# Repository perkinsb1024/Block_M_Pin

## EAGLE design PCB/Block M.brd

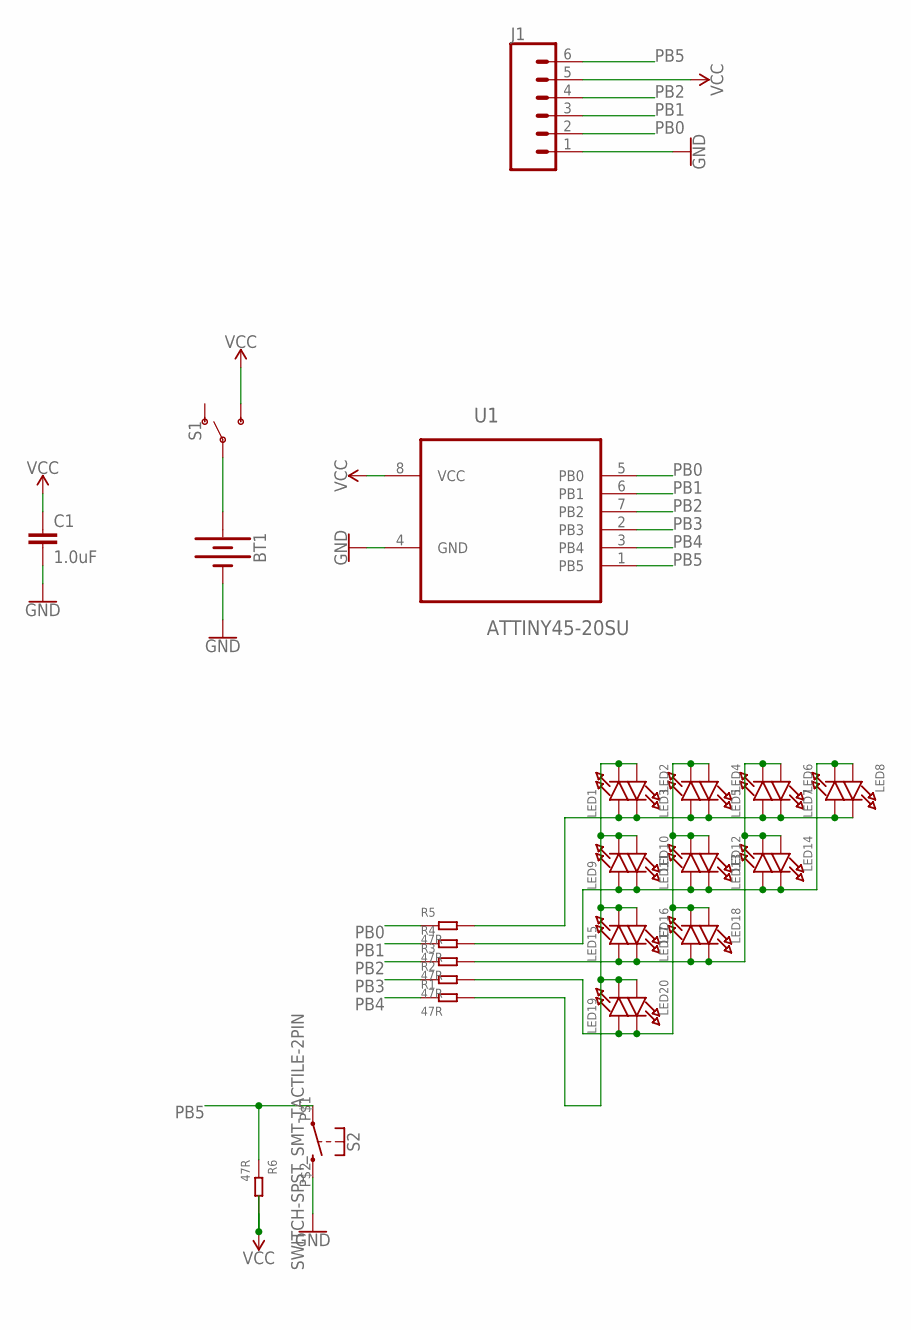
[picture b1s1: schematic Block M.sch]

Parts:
BT1: BATTERY-12MM_SMD_ALT; BATTCON_12MM_ALT
C1: 1.0uF; 0805
J1: CONN_06SMD-FEMALE-NO-SILK; 1X06-SMD-FEMALE_NO_SILK
LED1, LED2, LED3, LED4, LED5, LED6, LED7, LED8, LED9, LED10, LED11, LED12, LED13, LED14, LED15, LED16, LED17, LED18, LED19, LED20: LED0805_NOOUTLINE; CHIPLED_0805_NOOUTLINE
R1, R2, R3, R4, R5, R6: 47R; R0805
S1: SWITCH-SPDT-SMD-RIGHT-ANGLE; SWITCH_SPST_SMD_A
S2: SWITCH-SPST_SMT-TACTILE-2PIN; SMT_TACTILE_SWITCH_3X2MM
U1: ATTINY45-20SU; SOIC127P798X216-8N

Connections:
GND: BT1.GND (-), C1.2, J1.1, S2.P$2 (2), U1.4 (GND)
unnamed: LED1.A, LED2.C, LED3.A, LED4.C, LED5.A, LED6.C, LED7.A, LED8.C, R5.2
unnamed: BT1.PWR@2 (+), S1.2
unnamed: LED3.C, LED4.A, LED11.C, LED12.A, LED17.C, LED18.A, LED19.A, LED20.C, R2.2
unnamed: LED5.C, LED6.A, LED13.C, LED14.A, LED15.A, LED16.C, LED17.A, LED18.C, R3.2
unnamed: LED1.C, LED2.A, LED9.C, LED10.A, LED15.C, LED16.A, LED19.C, LED20.A, R1.2
unnamed: LED7.C, LED8.A, LED9.A, LED10.C, LED11.A, LED12.C, LED13.A, LED14.C, R4.2
PB0: J1.2, R5.1, U1.5 (PB0)
PB1: J1.3, R4.1, U1.6 (PB1)
PB2: J1.4, R3.1, U1.7 (PB2)
PB3: R2.1, U1.2 (PB3)
PB4: R1.1, U1.3 (PB4)
PB5: J1.6, R6.1, S2.P$1 (1), U1.1 (PB5)
VCC: C1.1, J1.5, R6.2, S1.3 (S), U1.8 (VCC)

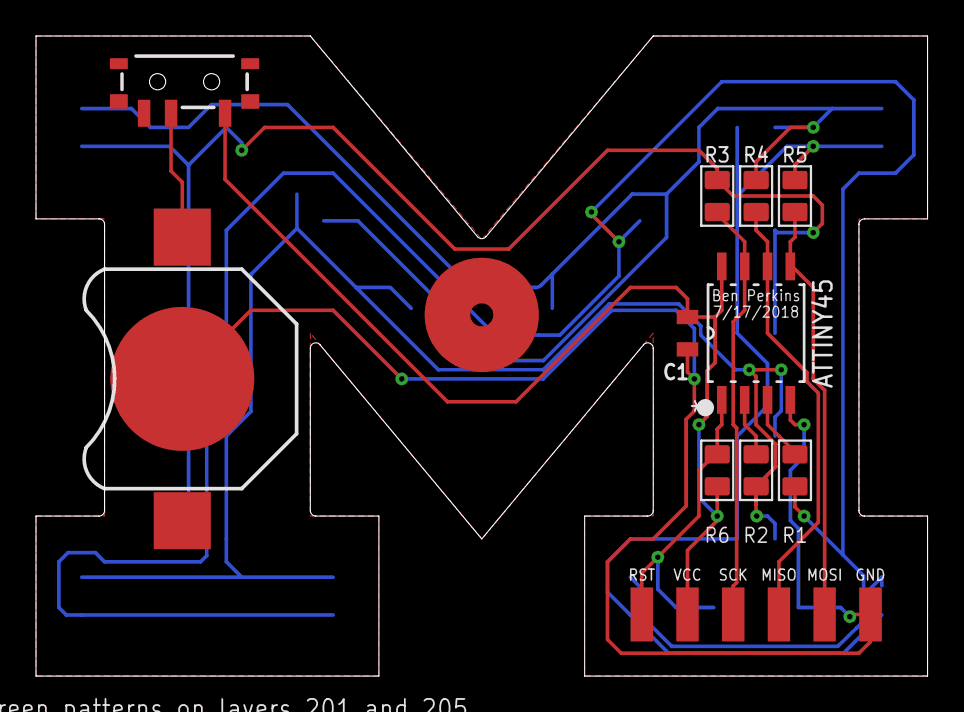
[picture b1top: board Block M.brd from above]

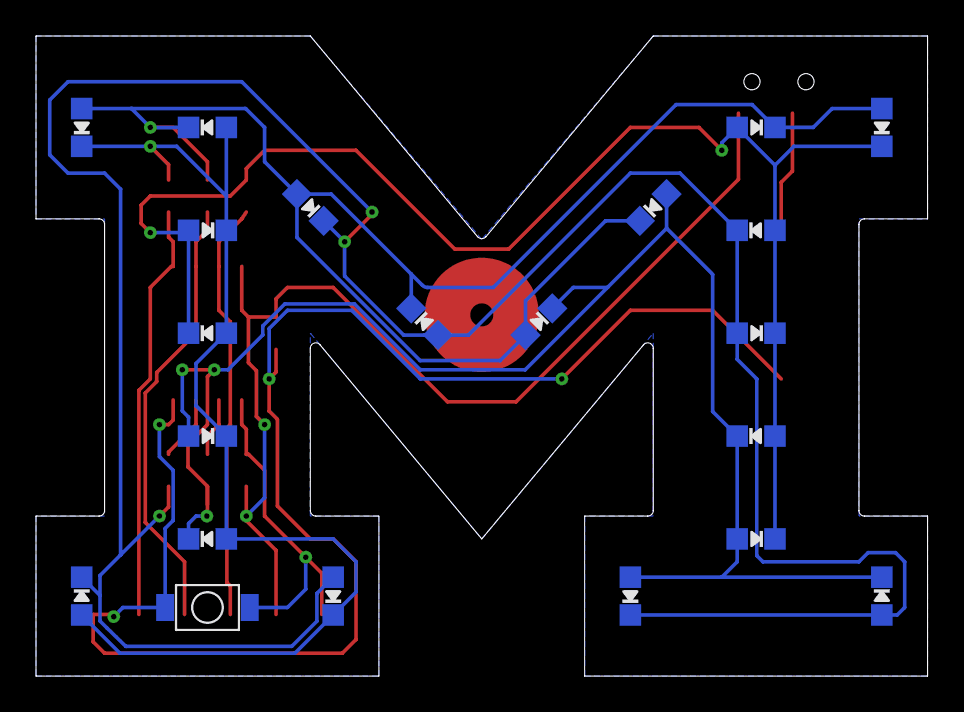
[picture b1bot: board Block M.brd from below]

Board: 2 copper layers, 49.5 x 35.6 mm, 32 parts (21 on the bottom side), 14 nets.

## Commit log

2018-07-28 Functional Charlie-Plexing. Could use some improvement
2018-07-28 Improved charlieplex logic. Reduced program size by 114 bytes (increased globals by 22 bytes). Improved speed and brightness
2018-07-30 Added more patterns and reduced MCU power consumption
2018-08-01 Added more patterns
2018-08-01 Improved 'boom' pattern
2018-08-01 Improved fade function
2018-08-01 Store seed for pRNG in EEPROM for more variability in 'randomness'
2018-08-05 Added function comments, cleaned code
2018-08-06 Added PCB files (Eagle and Gerber)
2018-08-06 Move Arduino Sketch into folder with the same name

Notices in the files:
parts and their libraries:
SparkFun-Switches: Licensing: Creative Commons ShareAlike 4.0 International - https://creativecommons.org/licenses/by-sa/4.0
microbuilder: This work is placed in the public domain, and may be freely used for commercial and non-commercial work with the following conditions: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
